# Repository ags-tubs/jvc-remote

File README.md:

JVC Remote
==========

### Usage ###

For interactive use inkvoke the script like this:<br />
`python3 -i listen.py`<br />
then you can call functions as follows:<br />
`>>>initCam()`<br />
`>>>sendCmd("Autoiris", 0)`<br />
`>>>sendKey("Iris", 127)`<br />

### Pinout ###

[26pin_studio_10pin_remote_6pin_tally.xls](cable_doku/26pin_studio_10pin_remote_6pin_tally.xls)

Es wird nur der Remote Anschluß benötigt.<br />
Der Stecker ist ein gewönlicher 6pin Mini-Din (der PS/2 Stecker) Anschluß.<br />
Zum Beispiel: <http://www.reichelt.de/SE-DIO-M06/3/index.html?&ACTION=3&LA=446&ARTICLE=17457&artnr=SE-DIO+M06>

Protokoll
---------

Signallevel: 3.3V<br />
Format: 9600baud 1E8 (8 daten, 1 stop-bit, even-parity)

### Protocol Flow ###

#### Typical Sequence ####
<table >
	<thead>
	<tr >
		<th  colspan="5"> Normal CCU to CAM flow </th>
	</tr>
	</thead>
	<tr >
		<th > Direction (seen from OCP) </th>
        <td >  TX       </td>
        <td >  RX  </td>
        <td >  TX   </td>
        <td >  RX  </td>
	</tr>
	<tr >
		<th > length (in Byte)            </th>
        <td >  1        </td>
        <td >  1   </td>
        <td >  3-4  </td>
        <td >  1   </td>
	</tr>
	<tr >
		<th > Purpose </th>
        <td > Startbyte </td>
        <td > ACK  </td>
        <td > Data </td>
        <td > ACK  </td>
	</tr>
</table>
Note: there is also the possibility to do CAM to CCU communication, <br />
which seems to be requested by a special char (0x90)

### Startbyte ###
<table >
	<thead>
	<tr >
		<th  colspan="9">  Startbyte    </th>
	</tr>
	</thead>
	<tr >
		<th > Bit      </th>
        <td >  0        </td>
        <td >  1  </td>
        <td >  2  </td>
        <td >  3  </td>
        <td >  4  </td>
        <td >  5  </td>
        <td >  6  </td>
        <td >  7  </td>
	</tr>
	<tr >
		<th> Purpose </th>
        <td> Transmission Start </td>
        <td colspan="2"> 0 </td>
        <td> Special </td>
        <td colspan="4"> data </td>
	</tr>
</table>
On normal (non special) transmission: treat data as number of bytes to be transmitted.<br />
If Special bit is set: data is the payload for the request this transmission was requested with. (see 3 byte data bitflags)

### Speculative interpretation of ACK byte: ###
<table>
   <tr>
    <th colspan="9">ACK byte</th>
   </tr>
   <tr>
    <th>Bit</th>
    <td>0</td>
    <td>1</td>
    <td>2</td>
    <td>3</td>
    <td>4</td>
    <td>5</td>
    <td>6</td>
    <td>7</td>
  </tr>
  <tr>
    <th>Funktion</th>
    <td> ACK</td>
    <td> UNIMPL </td>
    <td> ACK </td>
    <td> UNIMPL </td>
    <td colspan="2">0</td>
    <td> UNIMPL </td>
    <td> 0 </td>
  </tr>
</table>

0xA0 => transmission understood, everything OK<br />
0xF2 => transmission understood, but Feature not implemented

### Data bytes: ###
#### 4 Byte: ####

<table >
	<thead>
	<tr >
		<th  colspan="33">  Daten    </th>
	</tr>
	</thead>
	<tr >
		<th > Byte     </th>
        <td  colspan="8">  0  </td>
        <td  colspan="8">  1  </td>
        <td  colspan="8">  2  </td>
        <td  colspan="8">  3  </td>
	</tr>
	<tr >
		<th > Bit      </th>
        <td >  0  </td>
        <td >  1  </td>
        <td >  2  </td>
        <td >  3  </td>
        <td >  4  </td>
        <td >  5  </td>
        <td >  6  </td>
        <td >  7  </td>
        <td >  0  </td>
        <td >  1  </td>
        <td >  2  </td>
        <td >  3  </td>
        <td >  4  </td>
        <td >  5  </td>
        <td >  6  </td>
        <td >  7  </td>
        <td >  0  </td>
        <td >  1  </td>
        <td >  2  </td>
        <td >  3  </td>
        <td >  4  </td>
        <td >  5  </td>
        <td >  6  </td>
        <td >  7  </td>
        <td >  0  </td>
        <td >  1  </td>
        <td >  2  </td>
        <td >  3  </td>
        <td >  4  </td>
        <td >  5  </td>
        <td >  6  </td>
        <td >  7  </td>
	</tr>
	<tr >
		<th > Purpose </th>
        <td  colspan="12"> key </td>
        <td  > 0 </td>
        <td  colspan="11"> value </td>
        <td  colspan="8"> checksum </td>
	</tr>
</table>

#### 3 Byte: ####

<table >
	<thead>
	<tr >
		<th  colspan="25"> Data </th>
	</tr>
	</thead>
	<tr >
		<th > Byte     </th>
        <td  colspan="8">  0  </td>
        <td  colspan="8">  1  </td>
        <td  colspan="8">  2  </td>
	</tr>
	<tr >
		<th > Bit      </th>
        <td >  0  </td>
        <td >  1  </td>
        <td >  2  </td>
        <td >  3  </td>
        <td >  4  </td>
        <td >  5  </td>
        <td >  6  </td>
        <td >  7  </td>
        <td >  0  </td>
        <td >  1  </td>
        <td >  2  </td>
        <td >  3  </td>
        <td >  4  </td>
        <td >  5  </td>
        <td >  6  </td>
        <td >  7  </td>
        <td >  0  </td>
        <td >  1  </td>
        <td >  2  </td>
        <td >  3  </td>
        <td >  4  </td>
        <td >  5  </td>
        <td >  6  </td>
        <td >  7  </td>
	</tr>
	<tr >
		<th > Purpose </th>
        <td  colspan="8">  Command  </td>
        <td  colspan="4">  Bitflags  </td>
        <td  colspan="4">  Set Value </td>
        <td  colspan="8">  Checksum  </td>
	</tr>
</table>

Bitflags[2] = apply setting <br />
Bitflags[1] = request special transmission

### Features ###

This table was taken from cmds.csv wich was made by capturing the init sequence of CCU and CAM.<br />
With this handshake all available/unavailable Features should be negotiated.

####  cmd type ####
cmd => 3 byte<br />
key => 4 byte

#### setting ####
hex value for a specific setting (topic) <br />
must be treated differently for key and cmd

#### value ####
value to be set for the setting

#### bitfield ####
currently we are thinking these bits represet specific flags<br />
applies only to 3 byte commands; also see the section about 3 byte data

#### cam response ####
Response byte sent by the Camera,<br />
tells if the requested feature is available in the specific model.<br />
The following table was created by listening to communication with a JVC GM-HY251
//TODO: camera model?

#### topic ####
human readable representation of the setting-id<br />
for example cmd setting 0x07 is understood as gain control

#### value-representation ####
human readable representation of the values a setting can have.<br />
such as ON, OFF, incremental values, specific operation modes, ...

|cmd type|setting|value|bitfield|cam response|topic|value-representation|
|--------|-------|-----|--------|------------|-----|--------------------|
|cmd|0x00|0x0|0b0100|IMPL|Colorbars||
||||||||
|cmd|0x01|0x0|0b0100|IMPL|Detail||
||||||||
|cmd|0x02|0x0|0b0100|IMPL|Autoiris||
|cmd|0x02|0x1|0b0100|IMPL|Autoiris||
||||||||
|cmd|0x03|0x0|0b0100|IMPL|White Bal|Manual|
|cmd|0x03|0x1|0b0100|IMPL|White Bal|Preset|
|cmd|0x03|0x2|0b0100|IMPL|White Bal|A|
|cmd|0x03|0x3|0b0100|IMPL|White Bal|B|
|cmd|0x03|0xf|0b0100|IMPL|White Bal|full auto|
||||||||
|cmd|0x06|0x0|0b0110|UNIPLM|Auto White||
|cmd|0x06|0x1|0b0110|IMPL|Auto White||
||||||||
|cmd|0x07|0x0|0b0100|IMPL|Gain|0dB|
|cmd|0x07|0x1|0b0100|IMPL|Gain|6dB|
|cmd|0x07|0x2|0b0100|IMPL|Gain|9dB|
|cmd|0x07|0x3|0b0100|IMPL|Gain|12dB|
|cmd|0x07|0x4|0b0100|IMPL|Gain|18dB|
|cmd|0x07|0x5|0b0100|UNIPLM|Gain||
|cmd|0x07|0x6|0b0100|UNIPLM|Gain||
|cmd|0x07|0x8|0b0100|IMPL|Gain||
|cmd|0x07|0x8|0b0100|IMPL|Gain|ALC|
|cmd|0x07|0xa|0b0100|IMPL|Gain|3dB|
|cmd|0x07|0xe|0b0100|UNIPLM|Gain||
||||||||
|cmd|0x08|0x0|0b0100|IMPL|Tally PGM||
|cmd|0x08|0x1|0b0100|IMPL|Tally PGM||
||||||||
|cmd|0x09|0x0|0b0100|IMPL|Call||
|cmd|0x09|0x1|0b0100|IMPL|Call||
||||||||
|cmd|0x0b|0x0|0b0110|UNIPLM|||
||||||||
|cmd|0x0c|0x0|0b0100|IMPL|Shutter|off|
|cmd|0x0c|0x1|0b0100|UNIPLM|Shutter||
|cmd|0x0c|0x2|0b0100|IMPL|Shutter|1/120|
|cmd|0x0c|0x3|0b0100|IMPL|Shutter|1/250|
|cmd|0x0c|0x4|0b0100|IMPL|Shutter|1/500|
|cmd|0x0c|0x5|0b0100|IMPL|Shutter|1/1000|
|cmd|0x0c|0x6|0b0100|IMPL|Shutter|1/2000|
|cmd|0x0c|0xf|0b0100|UNIPLM|Shutter||
||||||||
|cmd|0x0f|0x0|0b0100|IMPL|Black Toe|unmod|
|cmd|0x0f|0x1|0b0100|IMPL|Black Toe|stretch|
|cmd|0x0f|0x2|0b0100|IMPL|Black Toe|compress|
||||||||
|cmd|0x1b|0x0|0b0100|UNIPLM|||
|cmd|0x1b|0x1|0b0100|UNIPLM|||
||||||||
|cmd|0x1c|0x0|0b0100|IMPL|Auto Knee||
||||||||
|cmd|0x1d|0x0|0b0100|IMPL|Gamma||
|cmd|0x1d|0x1|0b0100|IMPL|Gamma||
|cmd|0x1d|0x2|0b0100|IMPL|Gamma||
|cmd|0x1d|0x3|0b0100|IMPL|Gamma||
|cmd|0x1d|0x4|0b0100|IMPL|Gamma||
||||||||
|cmd|0x47|0x0|0b0100|IMPL|GENLOCK SC|0|
|cmd|0x47|0x1|0b0100|IMPL|GENLOCK SC|90|
|cmd|0x47|0x2|0b0100|IMPL|GENLOCK SC|180|
|cmd|0x47|0x3|0b0100|IMPL|GENLOCK SC|270|
||||||||
|cmd|0x4a|0x0|0b0100|IMPL|DNR||
||||||||
|cmd|0x4b|0x0|0b0100|UNIPLM|||
|cmd|0x4b|0x1|0b0100|UNIPLM|||
|cmd|0x4b|0x2|0b0100|UNIPLM|||
|cmd|0x4b|0xf|0b0100|UNIPLM|||
||||||||
|cmd|0x4c|0x0|0b0100|IMPL|||
|cmd|0x4c|0x1|0b0100|IMPL|||
|cmd|0x4c|0x2|0b0100|IMPL|||
|cmd|0x4c|0xf|0b0100|UNIPLM|||
||||||||
|cmd|0x4d|0x0|0b0100|IMPL|Skin Detail||
||||||||
|cmd|0x4e|0x1|0b0100|UNIPLM|||
||||||||
|cmd|0x4f|0x0|0b0100|UNIPLM|||
|cmd|0x4f|0x1|0b0100|UNIPLM|||
|cmd|0x4f|0x2|0b0100|UNIPLM|||
||||||||
|cmd|0x50|0x1|0b0100|IMPL|Full Auto Shooting||
||||||||
|cmd|0x51|0x0|0b0100|UNIPLM|||
|cmd|0x51|0x1|0b0100|UNIPLM|||
||||||||
|cmd|0x52|0x0|0b0100|IMPL|||
||||||||
|cmd|0x53|0x0|0b0100|IMPL|Tally PVW||
|cmd|0x53|0x1|0b0100|IMPL|Tally PVW||
||||||||
|cmd|0x7c|0x1|0b0100|IMPL|||
||||||||
|cmd|0x7d|0x1|0b0100|IMPL|||
||||||||
|key|0x00|0x340||IMPL|Iris||
||||||||
|key|0x02|||IMPL|Gain R||
||||||||
|key|0x03|||IMPL|Gain B||
||||||||
|key|0x06|||IMPL|Master Black||
||||||||
|key|0x12|0x530||UNIPLM|||
||||||||
|key|0x14|0x400||IMPL|||
||||||||
|key|0x16|0x400||IMPL|||
||||||||
|key|0x26|0x328||IMPL|Red||
|key|0x26|0x404||IMPL|Red||
||||||||
|key|0x27|0x230||IMPL|Blue||
|key|0x27|0x41c||IMPL|Blue||
||||||||
|key|0x32|0x604||IMPL|||
||||||||
|key|0x36|0x114||IMPL|Gamma Master||
||||||||
|key|0x37|0x114||IMPL|Gamma G||
||||||||
|key|0x40|0x340||IMPL|Autoiris||
||||||||
|key|0x56|0x26e||UNIPLM|||
||||||||
|key|0x74|0x801||UNIPLM|||
||||||||
|key|0xb4|0x801||UNIPLM|Genlock H Phase 1||
|key|0xb5|0x801||UNIPLM|Genlock H Phase 2||
||||||||
|key|0xf2|0x008||UNIPLM|||
|key|0xf2|0x00c||UNIPLM|||
|key|0xf2|0x80c||UNIPLM|||
||||||||
|key|0xf3|0x00c||UNIPLM|||
|key|0xf3|0xf7c||UNIPLM|||

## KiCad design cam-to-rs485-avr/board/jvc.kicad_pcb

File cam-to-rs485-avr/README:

This little subproject is an adaptor that can be used to establish a connection 
to a jvc (gy-hd/hm whatever) camera via a long symetric cable (eg XLR). 
No protocol conversion is done, only (more or less) intelligent switching 
between RE and DE at the MAX485.

Additionally there is a tally out that is switched by listening to the 
"Tally PGM" command.

an example setup:

PC => USB to 485 converter => XLR-Cable => 485 to JVC adapter => JVC camera

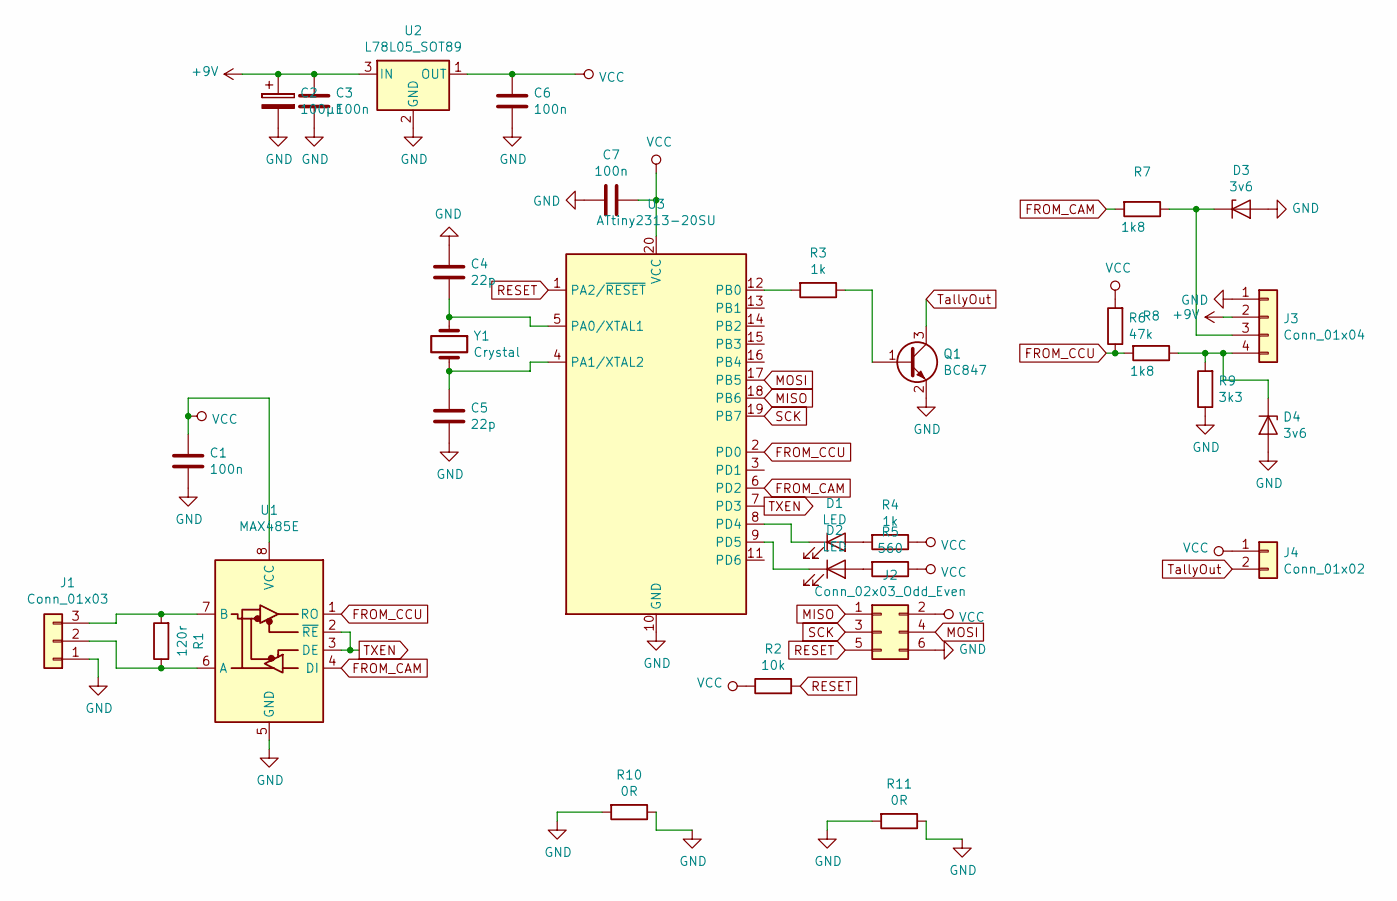
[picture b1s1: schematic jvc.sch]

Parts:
C1, C3, C6, C7: 100n; C_0805_2012Metric
C2: 100µF; CP_Elec_10x10.5
C4, C5: 22p; C_0805_2012Metric
D1, D2: LED; LED_0805_2012Metric
D3, D4: 3v6; D_MELF-RM10_Universal_Handsoldering
J1: Conn_01x03; PinHeader_1x03_P2.54mm_Vertical
J2: Conn_02x03_Odd_Even; PinHeader_2x03_P2.54mm_Vertical_SMD
J3: Conn_01x04; PinHeader_1x04_P2.54mm_Vertical
J4: Conn_01x02; PinHeader_1x02_P2.54mm_Vertical
Q1: BC847; SOT-23
R1: 120r; R_0805_2012Metric
R2: 10k; R_0805_2012Metric
R3, R4: 1k; R_0805_2012Metric
R5: 560; R_0805_2012Metric
R6: 47k; R_0805_2012Metric
R7, R8: 1k8; R_0805_2012Metric
R9: 3k3; R_0805_2012Metric
R10, R11: 0R; R_1206_3216Metric
U1: MAX485E; DIP-8_W7.62mm_Socket
U2: L78L05_SOT89; SOT-89-3
U3: ATtiny2313-20SU; SOIC-20W_7.5x12.8mm_P1.27mm
Y1: Crystal; Crystal_SMD_HC49-SD

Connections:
+9V: C2.1, C3.1, J3.2, U2.3 (IN)
FROM_CAM: R7.2, U1.4 (DI), U3.6 (PD2)
FROM_CCU: R6.1, R8.2, U1.1 (RO), U3.2 (PD0)
GND: C1.2, C2.2, C3.2, C4.1, C5.2, C6.1, C7.2, D3.2 (A), D4.2 (A), J1.1, J2.6, J3.1, Q1.2 (E), R9.1, R10.1, R10.2, R11.1, R11.2, U1.5 (GND), U2.2 (GND), U3.10 (GND)
MISO: J2.1, U3.18 (PB6)
MOSI: J2.4, U3.17 (PB5)
unnamed: C4.2, U3.5 (PA0/XTAL1), Y1.1
unnamed: C5.1, U3.4 (PA1/XTAL2), Y1.2
unnamed: D1.1 (K), U3.8 (PD4)
unnamed: D1.2 (A), R4.2
unnamed: D2.1 (K), U3.9 (PD5)
unnamed: D2.2 (A), R5.2
unnamed: D3.1 (K), J3.3, R7.1
unnamed: D4.1 (K), J3.4, R8.1, R9.2
unnamed: J1.2, R1.1, U1.6 (A)
unnamed: J1.3, R1.2, U1.7 (B)
unnamed: Q1.1 (B), R3.1
unnamed: R3.2, U3.12 (PB0)
RESET: J2.5, R2.2, U3.1 (PA2/~RESET)
SCK: J2.3, U3.19 (PB7)
TXEN: U1.2 (~RE), U1.3 (DE), U3.7 (PD3)
TallyOut: J4.2, Q1.3 (C)
VCC: C1.1, C6.2, C7.1, J2.2, J4.1, R2.1, R4.1, R5.1, R6.2, U1.8 (VCC), U2.1 (OUT), U3.20 (VCC)

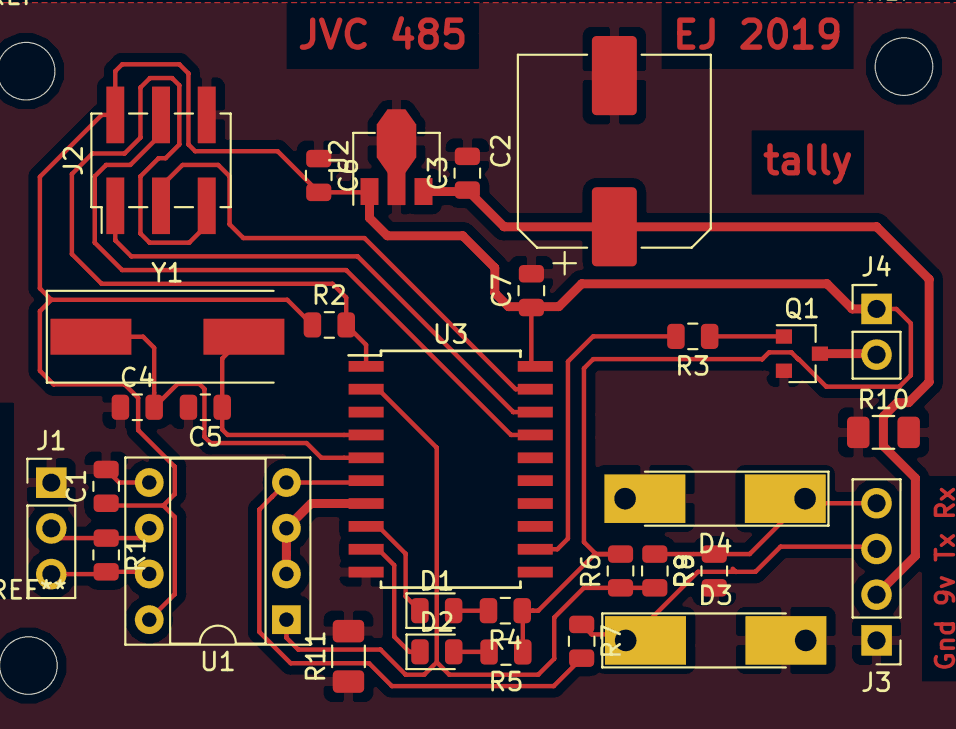
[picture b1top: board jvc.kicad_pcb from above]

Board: 2 copper layers, 31 parts (0 on the bottom side), 23 nets.

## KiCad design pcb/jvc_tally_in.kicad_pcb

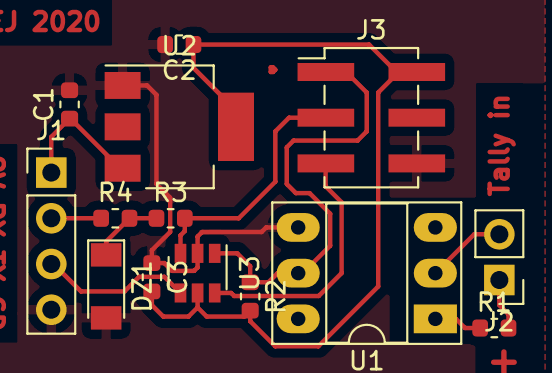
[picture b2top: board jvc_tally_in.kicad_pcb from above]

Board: 2 copper layers, 14 parts (0 on the bottom side), 12 nets.

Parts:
C1, C2: 10u; C_0603_1608Metric
C3: 100n; C_0603_1608Metric
DZ1: 3V3; D_MiniMELF
J1: Conn_01x04_Male; PinHeader_1x04_P2.54mm_Vertical
J2: Conn_01x02_Male; PinHeader_1x02_P2.54mm_Vertical
J3: Conn_02x03_Odd_Even; PinHeader_2x03_P2.54mm_Vertical_SMD
R1: 60R; R_0603_1608Metric
R2, R3, R4: 10k; R_0603_1608Metric
U1: CNY17-1; DIP-6_W7.62mm_Socket_LongPads
U2: LM1117-3.3; SOT-223-3_TabPin2
U3: ATtiny10-TS; SOT-23-6

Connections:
+3V3: C2.1, C3.2, J3.2, R2.2, U2.2, U3.5
+9V: C1.1, J1.1, U2.3
GND: C1.2, C2.2, C3.1, DZ1.2, J1.4, J3.6, U1.4, U2.1, U3.2
unnamed: DZ1.1, R3.1, R4.2
unnamed: J2.1, R1.2
unnamed: J2.2, U1.2
unnamed: R1.1, U1.1
RESET: J3.5, U3.6
RX: J1.2, R4.1
TPICLK: J3.3, R3.2, U3.3
TPIDATA: J3.1, R2.1, U1.5, U3.1
TX: J1.3, U3.4

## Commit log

2019-02-14 initial commit
    put work by lukas in git
2019-02-14 changed to what works for me
2019-02-14 listen to cam on 2nd uart + FAW
2019-02-14 more camera functions reversed
2019-02-14 tried remote in python
    does not work, because pyserial is crap
2019-02-14 pulseview log of startup sequence
2019-02-14 started remoting script with startupsequence
2019-02-15 dump of startup sequence by ccu
2019-02-15 messing around with startup sequence
2019-02-15 disable 2nd uart, since it was not very reliable
2019-02-15 move duku files
2019-02-15 mv pinout doku and add excel table from wiki
2019-02-15 Copy dokuwiki page by lukas to README
2019-02-15 update generator script for different sigrok
    My version: (sikrok-cli --version)
    sigrok-cli 0.7.1
    Libraries and features:
    - libsigrok 0.5.1/5:0:1 (rt: 0.6.0-git-0f523f2b/4:0:0).
    - Libs:
    - glib 2.56.1 (rt: 2.58.2/5802:2)
2019-02-16 swap CCU and CAM channels in trace file
2019-02-16 add support for reading from stdin
    serial read is untested for now
2019-02-16 print packet as hex array
2019-02-16 print (almost) human comprehensible conversation
    script crashes on exit, but doesnt matter; it prints everything it should.
    added interpretion of cam responses
    fix checksum for 3 byte cmds
2019-02-16 swap CAM and CCU channel
2019-02-16 dump analyse script
    can be used like this:
    dumps/dump_analyse.sh dumps/boot_jvc_neu.sr | ./listen.py
    or (more convenient when using always the same file):
    dumps/dump_analyse.sh dumps/boot_jvc_neu.sr > dmp.tmp
    cat dmp.tmp | ./listen.py
2019-02-17 change listener to just create a list of cmds ids
2019-02-17 create table for commad meanings
2019-02-17 add field for topic/setting/...
    manually added already known cmd ids to table
2019-02-17 include converted csv in README
2019-02-17 change representation of hex cmd to single digit
    since it is only a 4 bit value
2019-02-17 update doku to current knowing of the protocol
2019-02-17 translate to English and add some datails
2019-02-17 add description for columns
2019-02-17 csv of commands used in the referencing dumps
    funny to see the diff (vimdiff dumps/boot_jvc_alt.sr dumps/boot_jvc_neu.sr)
    conclusion: old jvc camera has more features than the newer one ...
2019-02-17 read commands from csv instead of hardcoded
2019-02-17 integrate csv from lister branch
2019-02-17 changes to make things work
    tested now with hardware and fixed all things that did not work
2019-02-17 autowhite trace
    autowhite => OK
    Iris close
    autowhite => error:low light
2019-02-18 add more insights to README
2019-02-18 add FAS mode
2019-02-18 remoteing and listening in fully working condition
    needs a bit of care on reading back values from camera
    init sequence runs reliable (with a bit of ugly hardcoded things) and
    should be more or less understandable.
    both listener and remote are using cmds.csv which contains all (by our
    camera) supported features
2019-02-18 new command ids
2019-02-19 few new features and shrink down init sequence
2019-02-19 add usage
2019-02-20 add always 0 field to documentation
2019-02-20 scanned all values from 0 to 0xFFF and dumped it
2019-02-21 Add LICENSE
2019-02-22 Schaltung für direkt an der Kamera um das 3,3V uart zeugs von der Kamera auf rs485 zu bekommen, ohne dafür das Protokoll zu dekodieren oder ähnliches
2019-02-22 Assign footprints
2019-02-22 add new cmd id meanings
2019-02-22 update cmd list and include README updater tool
2019-02-22 update readme, csv and update tool
2019-02-22 change debug prints
    and some other (dis)improvements on handling cam return values that i don't
    remember anymore
2019-02-23 485 Verlängerung as subprojekt fertig
    code könnte schöner werden, sehr viel hartkodiert
2020-02-14 initial commit
    testsetup for calibrating internal clock on 3.3V and 8MHz
2020-02-14 transmitting 'a' on 9600 baud
2020-02-15 working uart_putchar
    missing volatile before...
2020-02-15 move uart to new file
2020-02-15 defines for uart config
2020-02-16 even parity mode
2020-02-16 working rx
2020-02-17 turning color bars off and on
2020-02-17 tally software
2020-02-17 add pcb
2020-02-17 move code to 'code/'
2020-02-17 move to subfolder
2020-02-17 add README
